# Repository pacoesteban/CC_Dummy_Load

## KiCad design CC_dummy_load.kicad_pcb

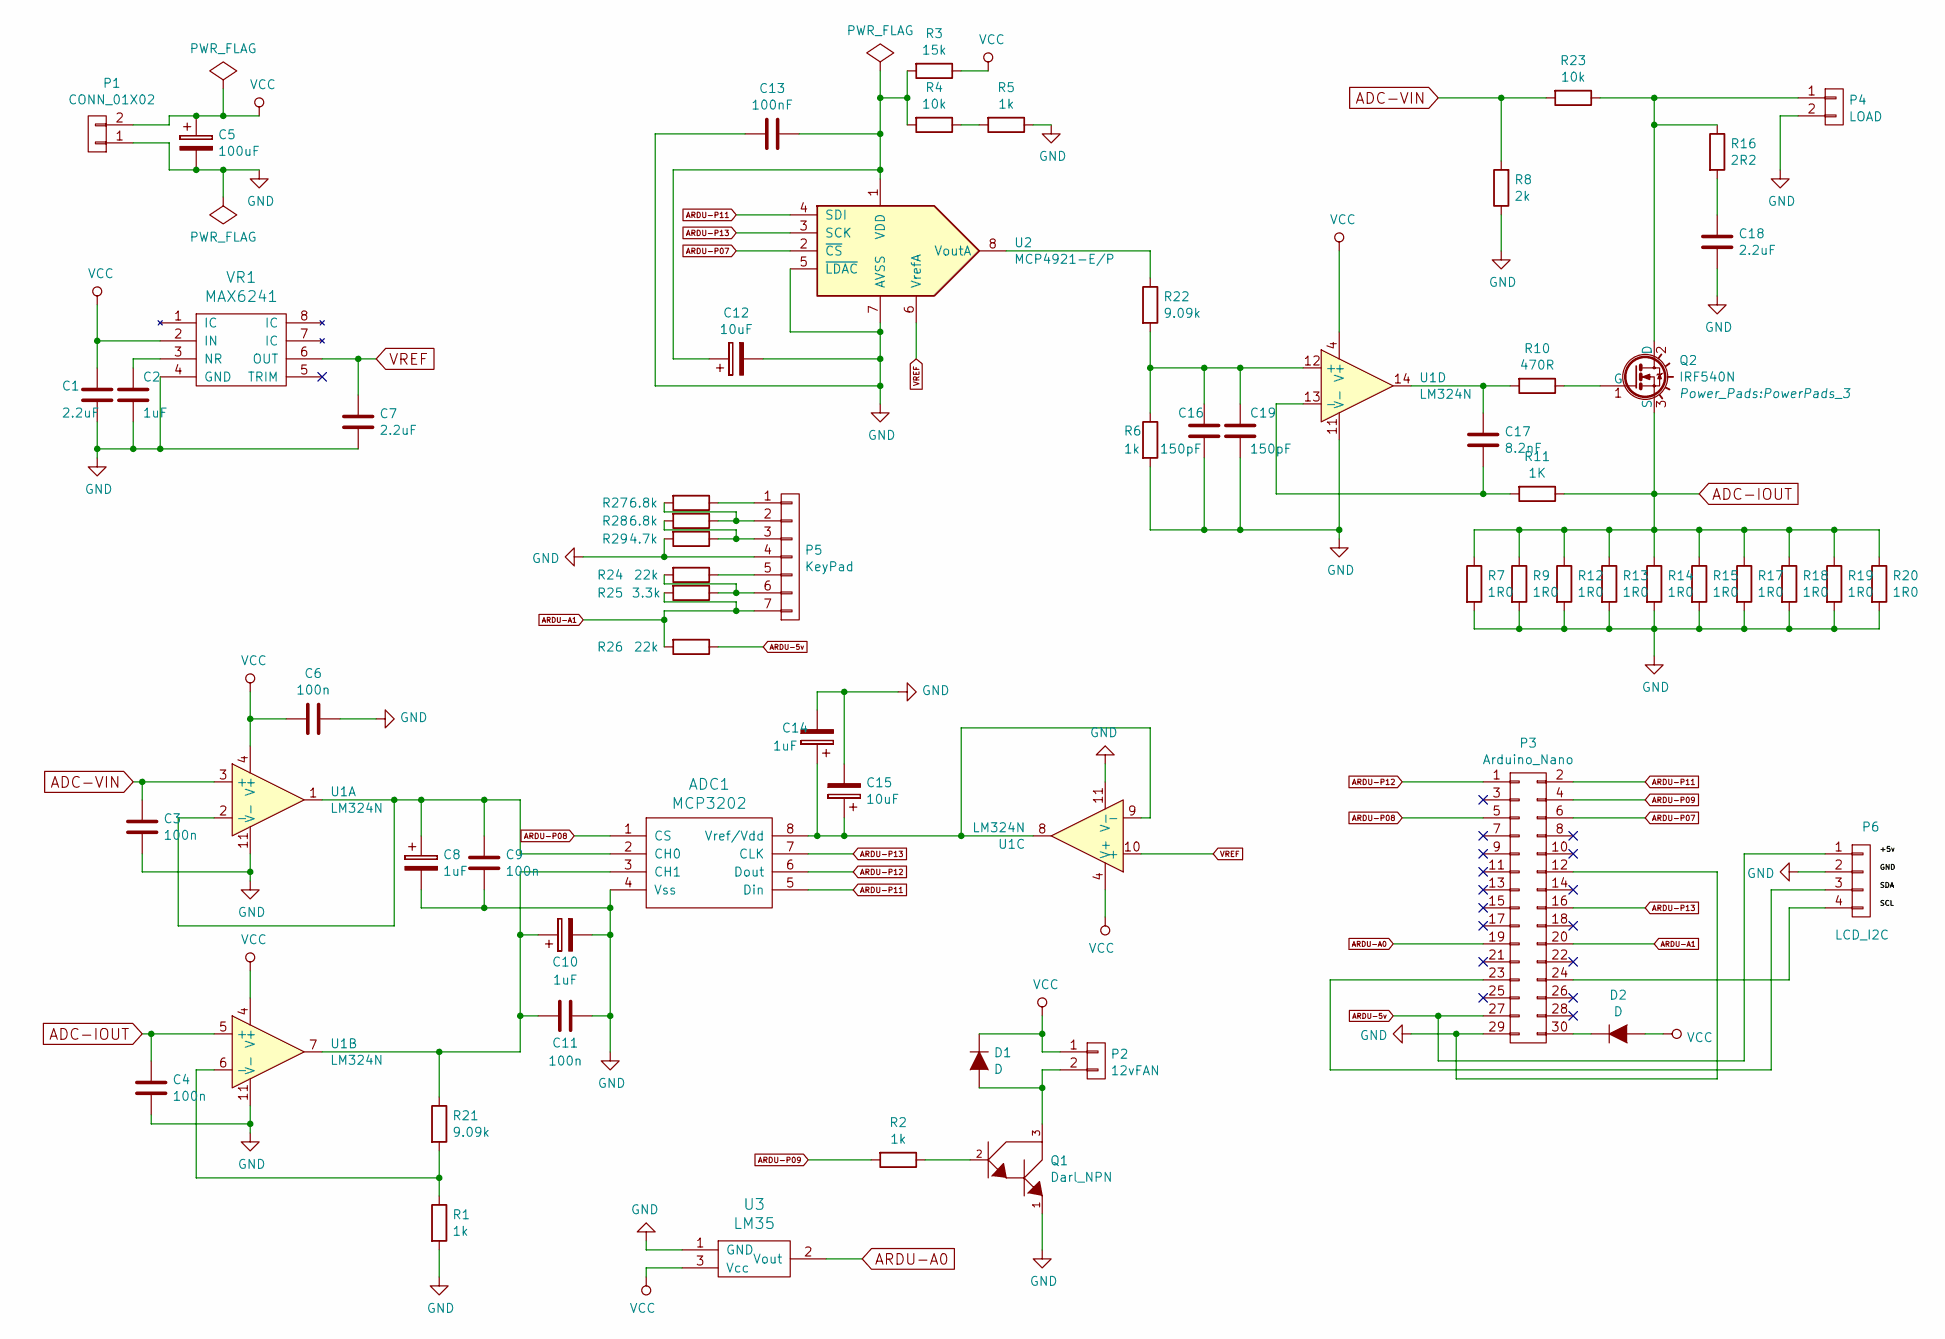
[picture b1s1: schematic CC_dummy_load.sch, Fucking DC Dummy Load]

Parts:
ADC1: MCP3202; DIP-8_W7.62mm
C1, C7, C18: 2.2uF; C_Disc_D6_P5
C2, C8, C10, C14: 1uF; C_Radial_D5_L11_P2
C3, C4, C6: 100n; C_Disc_D3_P2.5
C5: 100uF; C_Radial_D5_L11_P2.5
C9, C11: 100n; C_Disc_D6_P5
C12, C15: 10uF; C_Radial_D5_L11_P2
C13: 100nF; C_Disc_D6_P5
C16, C19: 150pF; C_Disc_D3_P2.5
C17: 8.2nF; C_Radial_D5_L11_P2
D1, D2: D; Diode_DO-41_SOD81_Horizontal_RM10
P1: CONN_01X02; bornier2
P2: 12vFAN; Pin_Header_Straight_1x02
P3: Arduino_Nano; Nano
P4: LOAD; bornier2
P5: KeyPad; Pin_Header_Straight_1x07
P6: LCD_I2C; Pin_Header_Straight_1x04
Q1: Darl_NPN; TO-92_Inline_Wide
Q2: IRF540N; PowerPads_3
R1, R2, R5, R6: 1k; Resistor_Horizontal_RM10mm
R3: 15k; Resistor_Horizontal_RM10mm
R4, R23: 10k; Resistor_Horizontal_RM10mm
R7, R9, R12, R13, R14, R15, R17, R18, R19, R20: 1R0; Resistor_Horizontal_RM10mm
R8: 2k; Resistor_Horizontal_RM10mm
R10: 470R; Resistor_Horizontal_RM10mm
R11: 1K; Resistor_Horizontal_RM10mm
R16: 2R2; Resistor_Horizontal_RM10mm
R21, R22: 9.09k; Resistor_Horizontal_RM10mm
R24, R26: 22k; Resistor_Horizontal_RM10mm
R25: 3.3k; Resistor_Horizontal_RM10mm
R27, R28: 6.8k; Resistor_Horizontal_RM10mm
R29: 4.7k; Resistor_Horizontal_RM10mm
U1: LM324N; DIP-14_W7.62mm
U2: MCP4921-E/P; DIP-8_W7.62mm
U3: LM35; Pin_Header_Straight_1x03
VR1: MAX6241; DIP-8_W7.62mm

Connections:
ADC-IOUT: C4.1, Q2.3 (S), R7.1, R9.1, R11.1, R12.1, R13.1, R14.1, R15.1, R17.1, R18.1, R19.1, R20.1, U1.5 (+)
ADC-VIN: C3.1, R8.2, R23.2, U1.3 (+)
ARDU-5v: P3.27, P6.1, R26.1
ARDU-A0: P3.19, U3.2 (Vout)
ARDU-A1: P3.20, P5.7, R25.2, R26.2
ARDU-P07: P3.6, U2.2 (~CS~)
ARDU-P08: ADC1.1 (CS), P3.5
ARDU-P09: P3.4, R2.2
ARDU-P11: ADC1.5 (Din), P3.2, U2.4 (SDI)
ARDU-P12: ADC1.6 (Dout), P3.1
ARDU-P13: ADC1.7 (CLK), P3.16, U2.3 (SCK)
GND: ADC1.4 (Vss), C1.2, C2.2, C3.2, C4.2, C5.2, C6.1, C7.2, C8.2, C9.2, C10.2, C11.1, C12.2, C13.2, C14.2, C15.2, C16.2, C18.2, C19.2, P1.1, P3.12, P3.29, P4.2, P5.4, P6.2, Q1.1, R1.2, R5.1, R6.2, R7.2, R8.1, R9.2, R12.2, R13.2, R14.2, R15.2, R17.2, R18.2, R19.2, R20.2, R29.2, U1.11 (V-), U2.5 (~LDAC~), U2.7 (AVSS), U3.1 (GND), VR1.4 (GND)
unnamed: ADC1.2 (CH0), C8.1, C9.1, U1.1, U1.2 (-)
unnamed: ADC1.3 (CH1), C10.1, C11.2, R21.1, U1.7
unnamed: ADC1.8 (Vref/Vdd), C14.1, C15.1, U1.8, U1.9 (-)
unnamed: C2.1, VR1.3 (NR)
unnamed: C12.1, C13.1, R3.2, R4.2, U2.1 (VDD)
unnamed: C16.1, C19.1, R6.1, R22.2, U1.12 (+)
unnamed: C17.1, R10.2, U1.14
unnamed: C17.2, R11.2, U1.13 (-)
unnamed: C18.1, R16.2
unnamed: D1.2 (A), P2.2, Q1.3
unnamed: D2.1 (K), P3.30
unnamed: P3.23, P6.3
unnamed: P3.24, P6.4
unnamed: P4.1, Q2.2 (D), R16.1, R23.1
unnamed: P5.1, R27.1
unnamed: P5.2, R27.2, R28.1
unnamed: P5.3, R28.2, R29.1
unnamed: P5.5, R24.1
unnamed: P5.6, R24.2, R25.1
unnamed: Q1.2, R2.1
unnamed: Q2.1 (G), R10.1
unnamed: R1.1, R21.2, U1.6 (-)
unnamed: R4.1, R5.2
unnamed: R22.1, U2.8 (VoutA)
VCC: C1.1, C5.1, C6.2, D1.1 (K), D2.2 (A), P1.2, P2.1, R3.1, U1.4 (V+), U3.3 (Vcc), VR1.2 (IN)
VREF: C7.1, U1.10 (+), U2.6 (VrefA), VR1.6 (OUT)

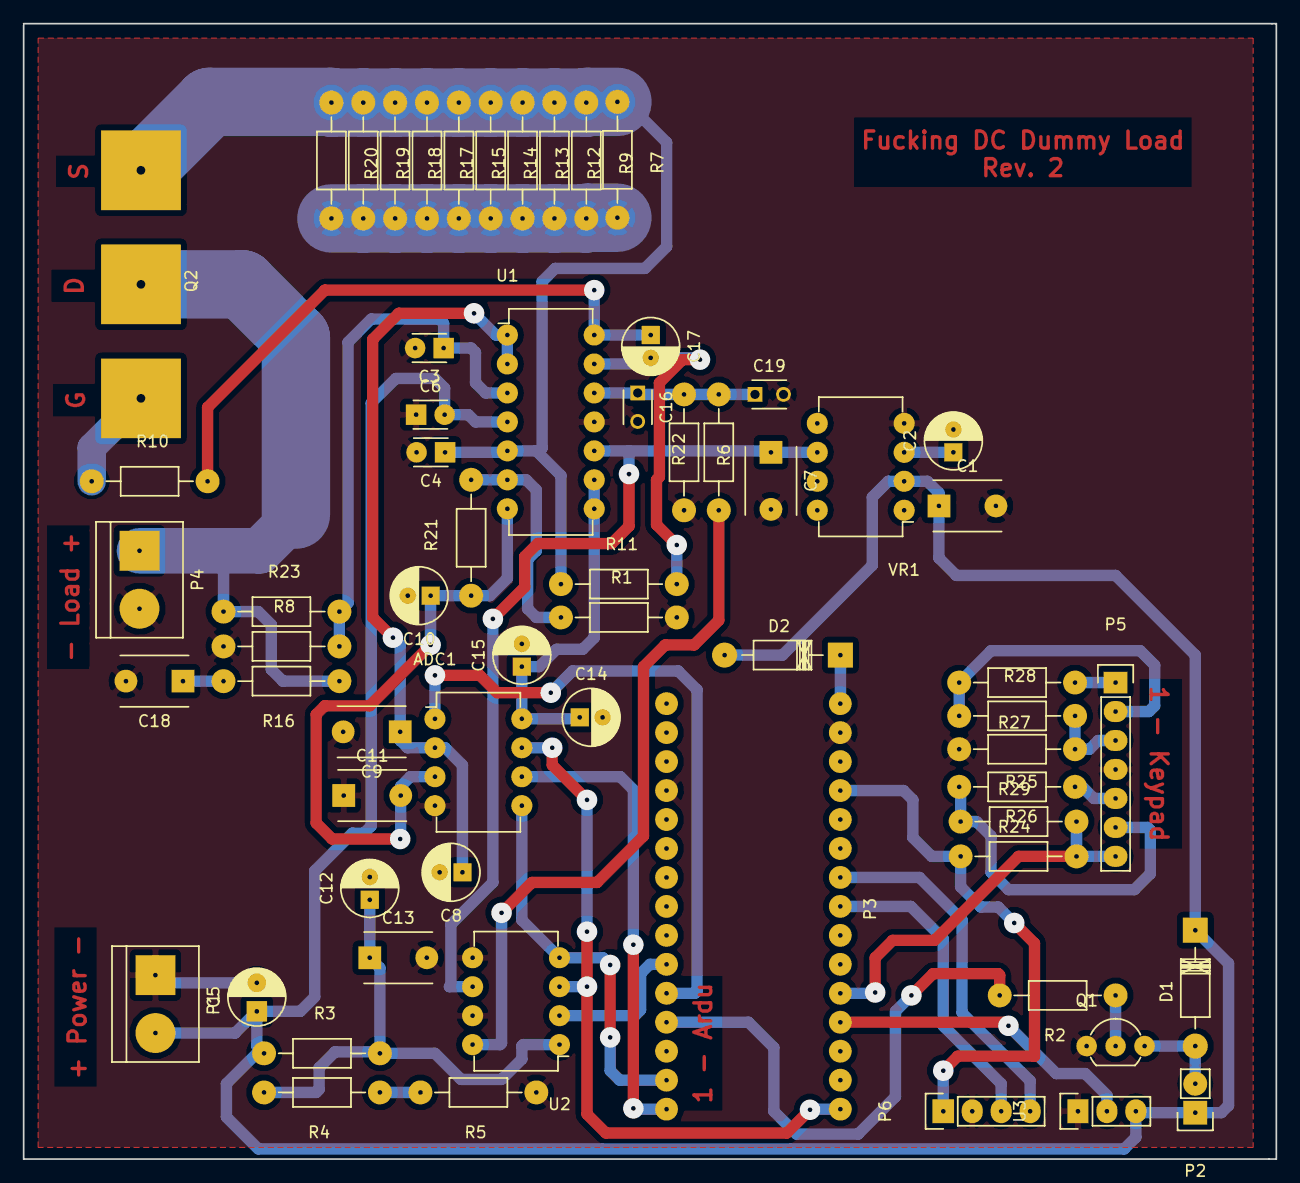
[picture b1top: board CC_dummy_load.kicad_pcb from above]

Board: 2 copper layers, 109.9 x 99.6 mm, 63 parts (0 on the bottom side), 38 nets.

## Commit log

2016-02-05 first working version
2016-02-05 adc code
2016-02-06 trying to fix ADC missreadings
2016-02-07 fixing amps reading on software because I suck at basic electrocnics
2016-02-10 fixes
2016-02-10 new input with floating point values
2016-02-10 improving display
2016-02-18 improvements
2016-02-19 final design v1
2016-02-19 change thermistor for LM35
2016-02-19 improvementss
2016-02-22 temperature limit cutoff
2016-02-24 associated components and starting to layout PCB
2016-02-25 PCB first version
2016-02-26 redesign with much more vias to be able to make it DIY
2016-02-26 more coper on back face
2016-03-09 rev 2
2016-03-17 mounting holes and stuff
2016-03-17 we can see temperature now while on load
2016-03-19 Revert "mounting holes and stuff"
    This reverts commit a6e826f9ddd28fcc19281836c77182ce96cc9986.
2016-03-19 ajustos previs al montatge i cagada temperatura
2016-04-06 so many changes
2016-04-08 Ardu no llegeix la etmp, passem a control de fan per Watts
2016-04-08 panell frontal
2016-04-08 mods panell frontal
2016-04-14 cleaning serial we do not need
2016-04-14 + and - on load
2016-04-14 constant resistance
2016-06-19 basic battery discharge
2016-06-20 adding serial output
2017-01-17 preparing for platformio
